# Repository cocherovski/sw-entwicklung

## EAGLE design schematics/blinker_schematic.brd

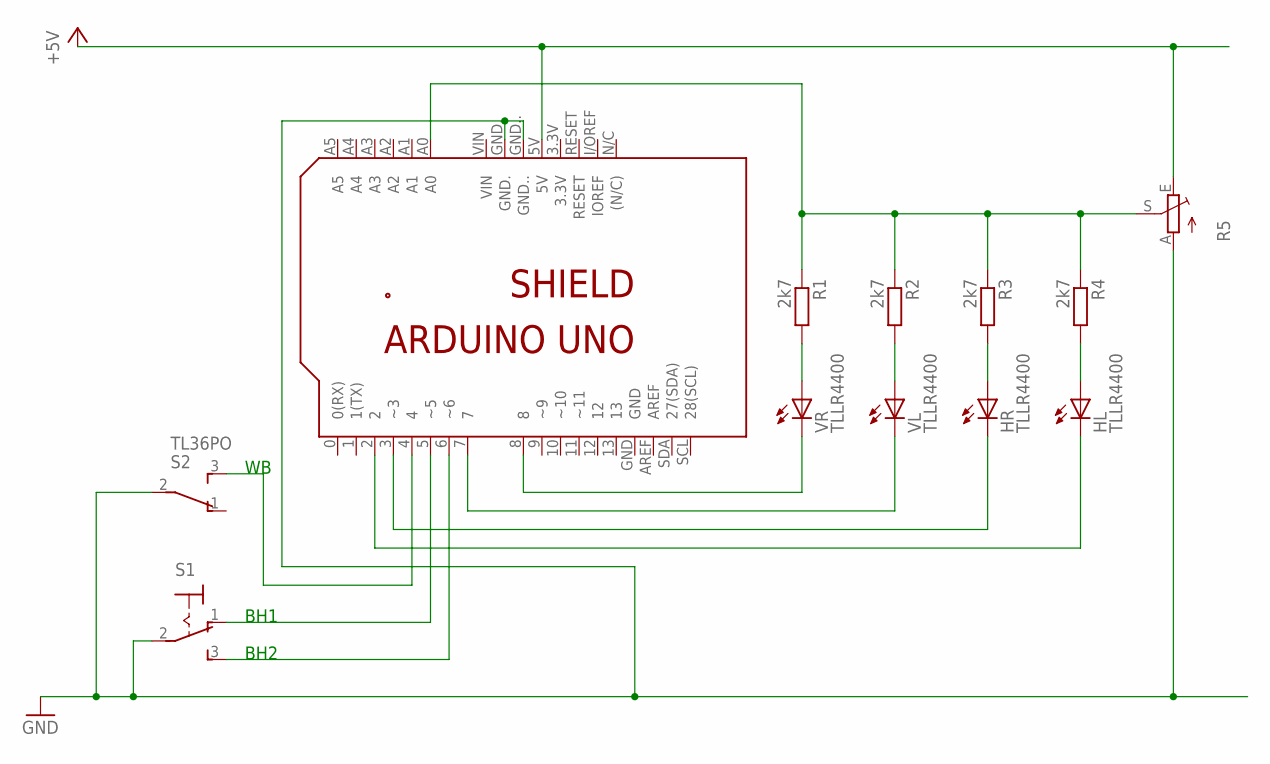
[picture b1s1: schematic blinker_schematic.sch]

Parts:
HL: TLLR4400; LED3MM
HR: TLLR4400; LED3MM
PCB1: ARDUINO_UNO
R1, R2, R3, R4: 2k7; 0207/12
R5: TRIM_EU-RS3; RS3
S1: M9040P
S2: TL36PO; TL3XPO
VL: TLLR4400; LED3MM
VR: TLLR4400; LED3MM

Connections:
+5V: PCB1.5V, R5.E
GND: PCB1.GND., PCB1.GND.., R5.A, S1.2, S2.2
unnamed: PCB1.A0, R1.1, R2.1, R3.1, R4.1, R5.S
unnamed: R1.2, VR.A
unnamed: R2.2, VL.A
unnamed: HR.A, R3.2
unnamed: HL.A, R4.2
unnamed: PCB1.8, VR.K (C)
unnamed: PCB1.7, VL.K (C)
unnamed: PCB1.6 (~6), S1.3 (S)
unnamed: PCB1.5 (~5), S1.1 (O)
unnamed: PCB1.4, S2.3 (S)
unnamed: HR.K (C), PCB1.3 (~3)
unnamed: HL.K (C), PCB1.2

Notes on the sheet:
BH1
BH2

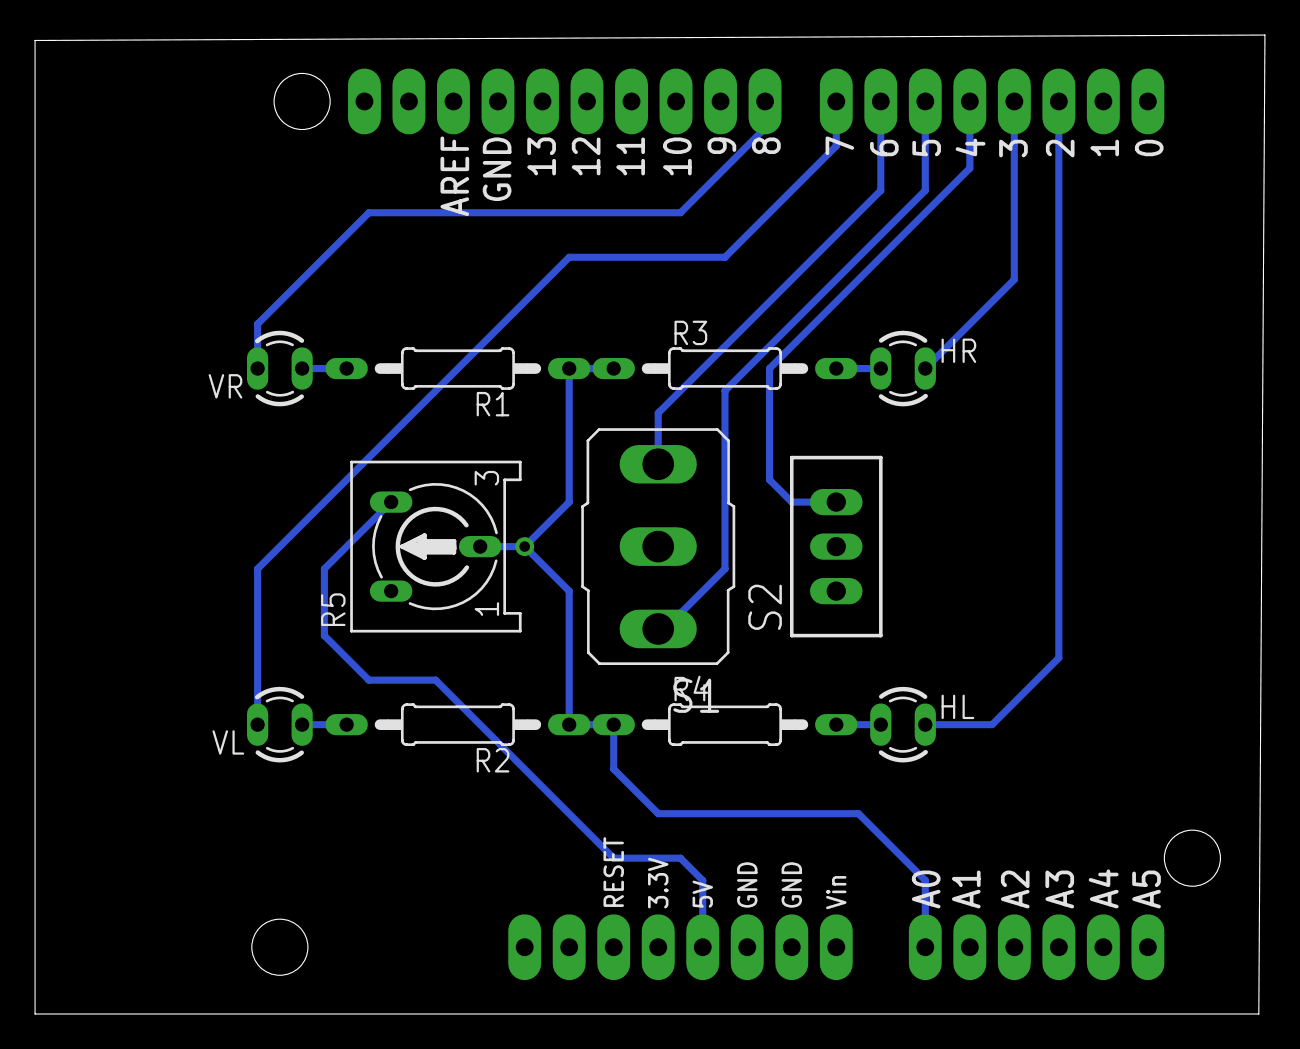
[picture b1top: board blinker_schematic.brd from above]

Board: 2 copper layers, 70.2 x 55.9 mm, 12 parts (0 on the bottom side), 14 nets.

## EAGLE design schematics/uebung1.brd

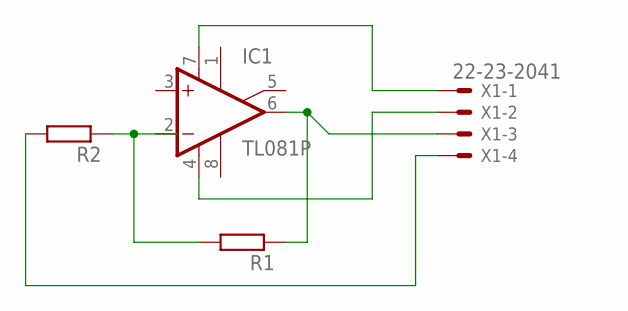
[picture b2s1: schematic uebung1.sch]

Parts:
IC1: TL081P; DIL08
R1, R2: R-EU_0207/10; 0207/10
X1: 22-23-2041

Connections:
unnamed: R1.2, R2.1
unnamed: IC1.6 (OUT), R1.1, X1.3
unnamed: R2.2, X1.4
unnamed: IC1.4 (V-), X1.2
unnamed: IC1.7 (V+), X1.1

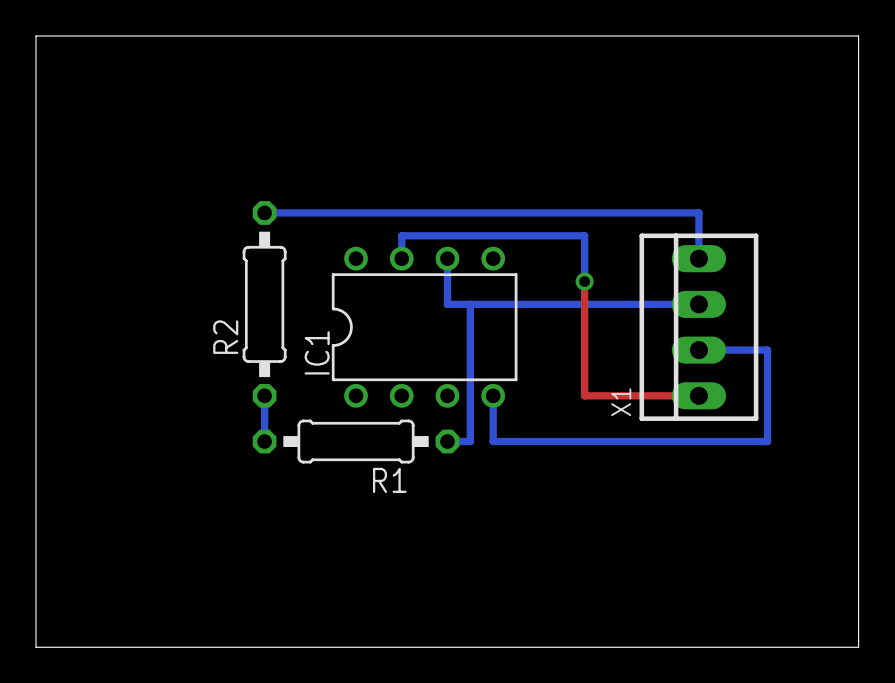
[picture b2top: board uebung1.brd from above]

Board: 2 copper layers, 45.7 x 34.0 mm, 4 parts (0 on the bottom side), 5 nets.

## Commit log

2016-09-26 Rename dreieckstausch.c to dreieckstausch.cpp
2016-09-26 Rename tankdeckel.cpp to tankteckel/tankdeckel.cpp
2016-09-26 Create a
2016-09-28 Create READM
